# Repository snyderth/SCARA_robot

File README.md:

# SCARA_robot
A SCARA topoology robotic arm

## Useful Documentation ##
 * [Altera FP IP Documentation](https://www.intel.com/content/www/us/en/programmable/documentation/eis1410764818924.html?wapkw=altfp_mult_ex_msim)

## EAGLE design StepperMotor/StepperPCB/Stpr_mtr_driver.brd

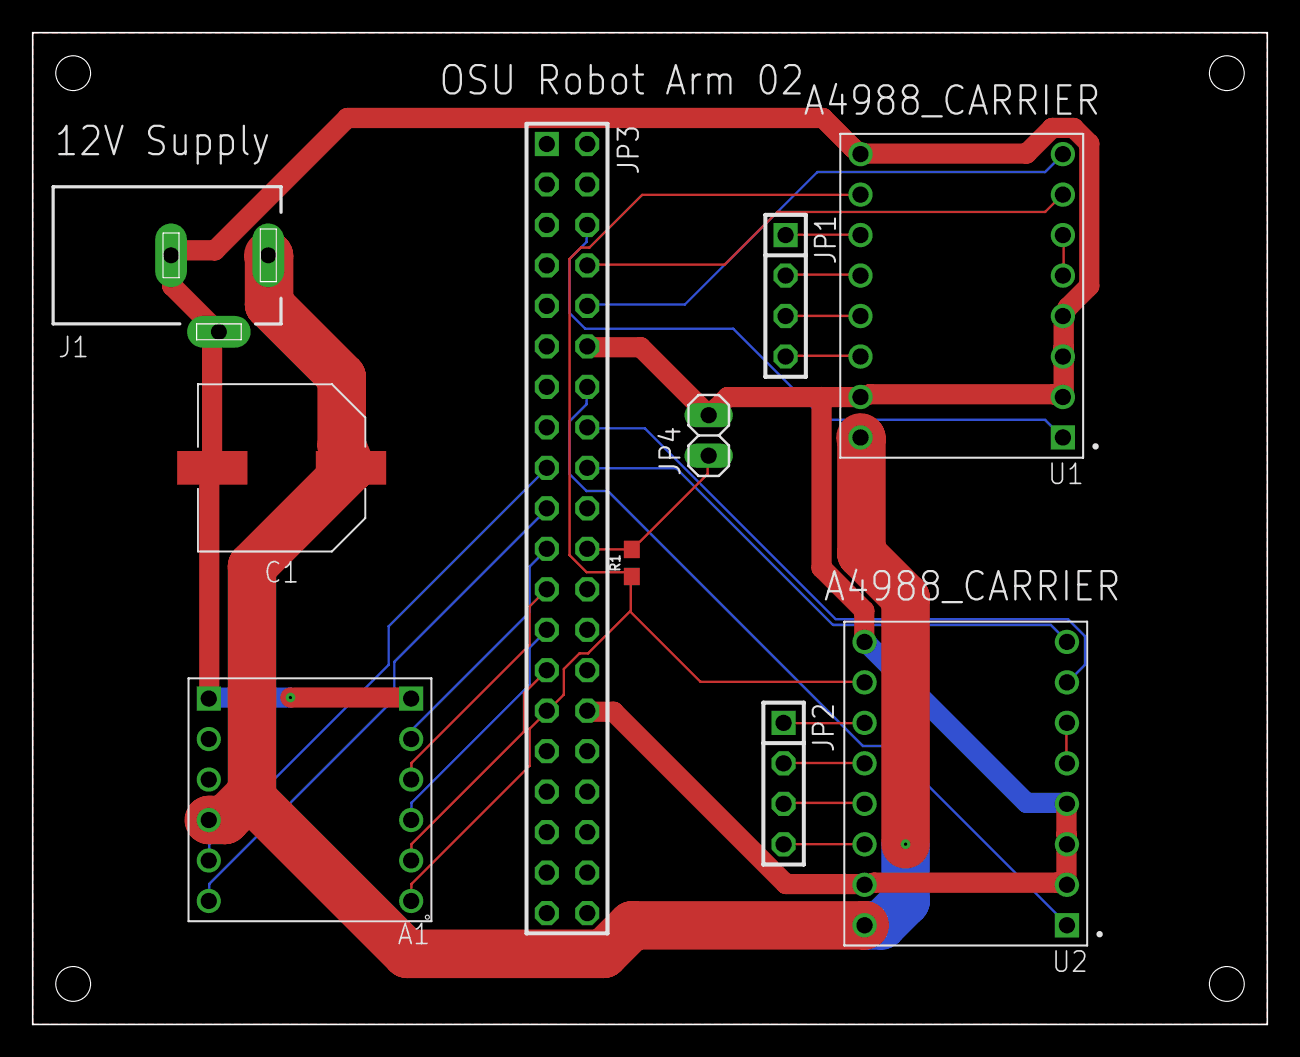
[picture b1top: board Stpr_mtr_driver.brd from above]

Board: 2 copper layers, 77.5 x 62.2 mm, 10 parts (0 on the bottom side), 26 nets.

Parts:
A1: DRV8801_CARRIER
C1: 100uF; CAPAE1030X1050N
J1: DCJ0303
JP1, JP2: 1X04
JP3: 2X20
JP4: 1X02
R1: 10k; 0603
U1, U2: A4988_STEPPER_MOTOR_DRIVER_CARRIER; MODULE_A4988_STEPPER_MOTOR_DRIVER_CARRIER

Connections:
3V3: A1.1, JP3.29, R1.1, U1.10, U2.10
12V: A1.9, C1.1, J1.1, U1.16, U2.16
B1: JP1.3, U1.13
B2: JP2.3, U2.13
BLK1: JP1.1, U1.11
BLK2: JP2.1, U2.11
BRAKE: A1.2, JP3.27
CUR_SENS: A1.8, JP3.17
DIR: A1.4, JP3.23
DIR1: JP3.10, U1.8
DIR2: JP3.18, U2.8
EN_N_1: JP3.6, U1.1
EN_N_2: JP3.14, U2.1
FAULT_N: A1.7, JP3.19
G1: JP1.2, U1.12
G2: JP2.2, U2.12
GND: A1.6, A1.12, C1.2, J1.2, J1.3, JP3.12, JP3.30, JP4.2, U1.2, U1.3, U1.4, U1.9, U1.15, U2.2, U2.3, U2.4, U2.9, U2.15
LIMIT: JP3.22, JP4.1, R1.2
unnamed: U1.5, U1.6
unnamed: U2.5, U2.6
PWM: A1.5, JP3.21
R1: JP1.4, U1.14
R2: JP2.4, U2.14
SLEEP_N: A1.3, JP3.25
STEP1: JP3.8, U1.7
STEP2: JP3.16, U2.7

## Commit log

2019-12-06 Basic architecture for gcode-formatter and vision modules.
2019-12-11 Messy unfinished edge detection code.
2019-12-11 Got hue coercement working.
2019-12-11 Started work on edge detection
2019-12-14 Image can be converted into lines.
2019-12-14 G code can now be generated from an image!
2019-12-14 beginning inverse kinematics simulator in python for both jacobian method and iterative FABRIK method
2019-12-19 Added simulation for inverse kinematics. FABRIK
2019-12-27 Initial code for gcode parser.
2019-12-27 Put testing into source files as __main__ function. Implemented gcode parsing.
2019-12-28 Changed parser to change argument units to something that uses the entire 14 bit argument space.
2019-12-30 fixing inverse kinematics algorithm
2020-01-01 Syncing animation working, but axes need to be rescaled.
2020-01-02 Fixed animation scaling. Animation smoothly performs for points around (7,7), but skips for all other points
2020-01-02 Animation works fully
2020-01-02 added requirements file for pip
2020-01-10 Began working on documentation for python. Set up project for GCode interpreter on fpga.
2020-01-19 Added inverse jacobian functionality
2020-01-30 Trying to add stepper motor blocks.
2020-01-30 Renaming folders
2020-01-30 trying out sphinx for docs
2020-01-30 moving things around for better organization
2020-01-30 removing index
2020-01-31 Added file comment to top of vision.py.
2020-01-31 Documenting
2020-02-01 Updated IK simulator with unit conversion and began implementing in FPGA
2020-02-01 Created test project for block checkoff.
2020-02-03 added an integer sin/cos function that outputs 64-bit floating point numbers. This may need to pair down to 32-bit
2020-02-04 Adding GUI python file.
2020-02-04 Removed placeholder file
2020-02-04 Adding forawrd kinematics and IP blocks
2020-02-05 Created controller interface module
2020-02-05 Starting work on c interface to hps.
2020-02-06 made progress on 2nd block. Added testing to gcode parser
2020-02-06 Almost finished with forward kinematics. Issues in the add and multiply blocks with sync signals
2020-02-07 Made progress on .sv test files. Still not done.
2020-02-07 fixed issues with add and muliply floating point doubles
2020-02-07 Implemented block 2 to the best to my abilities. Still needs more perfecting.
2020-02-07 Forward kinematics are fully functional
2020-02-07 Added Jacobian calculations and organized the main file to contain a state machine
2020-02-10 Simulating Jacobian. Does not work. Data ready signals are not triggering on the multiplication blocks
2020-02-12 Jacobian logic is now working and tested in simulation
2020-02-13 Made parser more robust, fixed tool change units issue.
2020-02-13 Changed FPGA Gcode Interpreter Test to be top level FPGA
2020-02-14 Finished Jacobian. Moving to Jacobian inverse
2020-02-14 Generated division IP
2020-02-14 Trying to fix division simulation. The simulator keeps crashing after throwning an error that a parameter in the auto-generated IP is incorrect. Maybe I'll try to regenerate it at home, but I think t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
2020-02-14 Edit readme
2020-02-14 Adding Jacobian Inverse to controller top level module
2020-02-14 Fixed problem of negative numbers not being represented properly.
2020-02-14 Added up to multiply out step. Now need to convert dtheta to steps and possibly add an accumulator. Some issues may now be encountered with the 14-bit x and y targets, so conversion to 32-bits may ne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
2020-02-14 Added steps to degrees conversion and fixed the dx dy selection
2020-02-14 oh god I edited without pulling help
2020-02-14 Added INIT state to controller
2020-02-16 Got line interpolation working and somewhat tested for the absolute positioning case.
2020-02-16 Better documentation for gcodeParser
2020-02-16 Controller Inverse Kinematics fully running. I believe I have an issue with the forward kinematics that needs to be solved
2020-02-17 Fixed SCARA controller calculations. Adding in a checking state to check when it is done
2020-02-17 Created simpler interface to gcode sending for GUI.
2020-02-18 Converted finish check to state machine
2020-02-18 Pivoting to new controller with closed form solutions
2020-02-18 Created the necessary Arctan2 function. Attempting to simulate but getting issues in some of the altera IP when running
2020-02-20 Added sin(th2) and cos(th2) blocks for arithmentic. Cosine block is simulated. Sine block is not
2020-02-20 More of the control algorithm is done
2020-02-20 Working on sending data back from FPGA.
2020-02-21 Control math is working and tested in simulation
2020-02-21 Syncing
2020-02-22 Verified functionality of command interface.
2020-02-22 Inverse kinematics done. need to build the blocks around it
2020-02-22 Added state machine to the conversion
2020-02-22 Scara Controller Fully functional
2020-02-22 Committing some things that did not commit last time.
2020-02-22 Fixed Calculate Steps block
2020-02-23 fixed Atan2. Moving on to altfp_add_sub
2020-02-23 Committing for Thomas :)
2020-02-23 Made conversion more granular to fit entire -11 to 11 inch space.
2020-02-23 Commented stuff for Thomas.
2020-02-23 Fixed logic error in reset, adjust speed for long step instructions.
2020-02-23 Using a single atan block in calculateangles
2020-02-23 Added simulation
2020-02-23 Extra commit stuff
2020-02-23 readded stp_counter.sv which became untracked on rename.
2020-02-23 Pipelining controller functions for space efficiency
2020-02-23 adding calculate angles
2020-02-23 Committing to pull
2020-02-23 Fixing Pipelines
2020-02-23 Realized I had the wrong device in the project. Space issues resolved
2020-02-23 Test commit: WiP DC Motor Driver template
2020-02-23 Added extra function to easycall to make it easier.
2020-02-23 Fixed some weird merge error.
2020-02-23 commiting simulation files
2020-02-23 Fixed import problem in gcodeParser.py
2020-02-24 Finished scara controller
2020-02-24 Adding gui stuff and updating DCMotor
2020-02-24 Added some temporary GUI reporting functionality
2020-02-24 Simulation madness
2020-02-24 Even more simulation stuff
2020-02-24 Got simulation working working on debugging now.
2020-02-25 Finished the DCMotor driver block. Added sim file.
2020-02-25 Got stuff closer to working. Simulated stuff seems to work and now we need to get things working on the metal.
2020-02-26 Added signal tap file.
2020-02-26 New step file
2020-02-26 SRLatch is cancelled.
2020-02-27 simplified step_length
2020-02-27 Fixing code.
2020-02-28 Working on serial interface for GUI. FPGA code is approaching a working state.
2020-02-29 Easy call, easy life.
2020-02-29 Changed relative vs absolute
2020-02-29 Pushing changes to the scara controller and calculate angles blocks that add relative movement calculations
2020-02-29 Worked on debugging
2020-03-01 Backing up work in process.
2020-03-01 Restructured GUI to be less jarring. Corrected circular imports.
2020-03-01 Reformatted a lines. Forced the width of uploaded image to fit in GUI window.
2020-03-01 Added some code comments, changed the theme, and made the GUI more user-friendly/readable.
2020-03-01 Working on debugging
2020-03-02 Merging files changed on the FPGA with files on my computer. Removed interpolation because it was not working an is no longer needed. Added CommandSender.py as another testing interface.
2020-03-03 Adding line mapping for point shifting to lineaize arm movements
2020-03-03 Refactored simulation to only have geometric method
2020-03-04 Backing up changed files.
2020-03-04 Changed conversion
2020-03-04 Constraining the scara_ik points to be in bounds
2020-03-05 Created SFTP interface to board.
2020-03-05 Made ftp not require file name to be test.gcode. Added missing files.
2020-03-05 Can only open GCode file now.
2020-03-05 Fixing the end effector state logic
2020-03-05 Got end effector simulating properly
2020-03-05 Compiled changes
2020-03-05 Adding header comments to source files
2020-03-05 updating .gitignore
2020-03-06 Committing changes
2020-03-11 Adding comments
2020-03-14 Added mechanical drawings
2020-03-27 Create LICENSE

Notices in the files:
parts and their libraries:
SparkFun-Resistors: Licensing: Creative Commons ShareAlike 4.0 International - https://creativecommons.org/licenses/by-sa/4.0
